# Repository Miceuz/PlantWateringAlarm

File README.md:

PlantWateringAlarm
==================

A soil moisture level sensor based on ATTINY44. Uses capacitive sensing.

More info at http://wemakethings.net/chirp

Contact: mic a wemakethings.net

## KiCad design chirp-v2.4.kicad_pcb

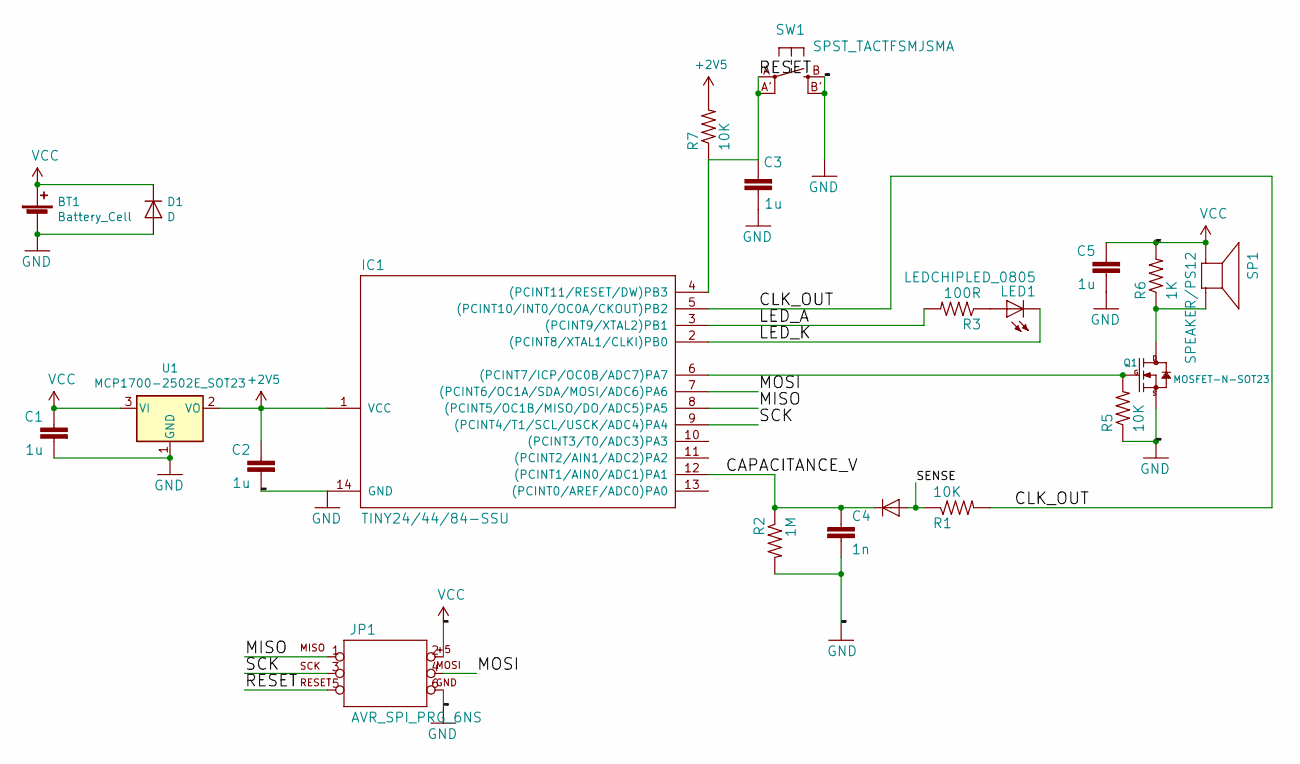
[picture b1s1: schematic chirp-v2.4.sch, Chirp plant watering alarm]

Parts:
BT1: Battery_Cell
C1: 1u; C_0603_1608Metric; PartNo ?
C2, C3, C5: 1u; C_0603_1608Metric
C4: 1n; C_0603_1608Metric
D1: D
D2: DIODE-SCHOTTKY_; SOD-523; PartNo ?
IC1: TINY24/44/84-SSU; SOIC-14_3.9x8.7mm_Pitch1.27mm; PartNo ?
JP1: AVR_SPI_PRG_6NS; 2X3-NS
LED1: LEDCHIPLED_0805; CHIPLED_0805
Q1: MOSFET-N-SOT23; SOT-23
R1, R5, R7: 10K; R_0603_1608Metric
R2: 1M; R_0603_1608Metric; PartNo ?
R3: 100R; R_0603_1608Metric
R6: 1K; R_0603_1608Metric
SP1: SPEAKER/PS12; PS12
SW1: SPST_TACTFSMJSMA; FSMJSMA
U1: MCP1700-2502E_SOT23; SOT-23; PartNo ?

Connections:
+2V5: C2.1, IC1.1 (VCC), R7.2, U1.2 (VO)
/CAPACITANCE_V: C4.1, D2.K (C), IC1.12 ((PCINT1/AIN0/ADC1)PA1), R2.1
/CLK_OUT: IC1.5 ((PCINT10/INT0/OC0A/CKOUT)PB2), R1.2
/LED_A: IC1.3 ((PCINT9/XTAL2)PB1), R3.2
/LED_K: IC1.2 ((PCINT8/XTAL1/CLKI)PB0), LED1.C
/MISO: IC1.8 ((PCINT5/OC1B/MISO/DO/ADC5)PA5), JP1.1
/MOSI: IC1.7 ((PCINT6/OC1A/SDA/MOSI/ADC6)PA6), JP1.4
/RESET: C3.1, IC1.4 ((PCINT11/RESET/DW)PB3), JP1.5, R7.1, SW1.A, SW1.A' (P1)
/SCK: IC1.9 ((PCINT4/T1/SCL/USCK/ADC4)PA4), JP1.3
/SENSE: D2.A, R1.1
GND: BT1.2 (-), C1.2, C2.2, C3.2, C4.2, C5.2, D1.2 (A), IC1.14 (GND), JP1.6, Q1.2 (S), R2.2, R5.1, SW1.B (S), SW1.B' (S1), U1.1 (GND)
unnamed: IC1.6 ((PCINT7/ICP/OC0B/ADC7)PA7), Q1.1 (G), R5.2
unnamed: LED1.A, R3.1
unnamed: Q1.3 (D), R6.1, SP1.P$2 (-)
VCC: BT1.1 (+), BT1.3, C1.1, C5.1, D1.1 (K), JP1.2, R6.2, SP1.P$1 (+), U1.3 (VI)

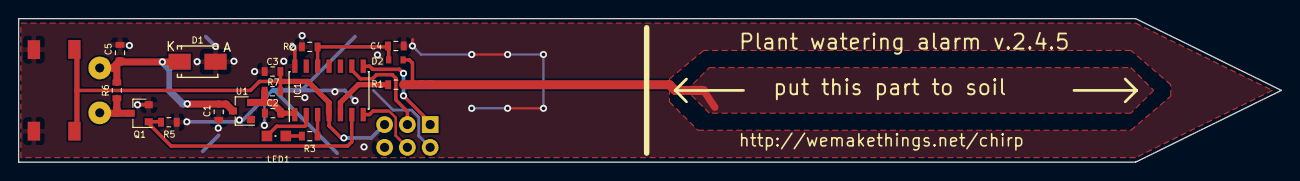
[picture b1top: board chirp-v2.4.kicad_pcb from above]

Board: 2 copper layers, 140.8 x 16.0 mm, 21 parts (0 on the bottom side), 15 nets.

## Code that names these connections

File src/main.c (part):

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#include <avr/eeprom.h>
#include "usiTwiSlave.h"

#define USI_SCK PA4
#define USI_MISO PA5
#define USI_CS PA6
#define BUZZER PA7
#define BUTTON PB2
#define LED_K PB0 
#define LED_A PB1

//------------ peripherals ----------------

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}

void inline ledOff() {
  DDRB &= ~(_BV(LED_A) | _BV(LED_K)); //make pins inputs
  PORTB &= ~(_BV(LED_A) | _BV(LED_K));//disable pullups
}

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    DDRA |= _BV(BUZZER);   //piezo buzzer
    PORTA &= ~_BV(BUZZER);
    
    DDRB |= _BV(PB0);   //nothing
    PORTB &= ~_BV(PB0);
    DDRB |= _BV(PB1);   //nothing
    PORTB &= ~_BV(PB1);
    DDRB |= _BV(PB2);   //square wave output
    PORTB &= ~_BV(PB2);
}

void inline setupPowerSaving() {
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    uint16_t result = getADC1();
    
    stopExcitationSignal();
    PORTB &= ~_BV(PB2);
    PRR |= _BV(PRTIM0);
    
    ADCSRA &=~ _BV(ADEN);
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    TCCR1A = 0;
    TCCR1B = _BV(CS12);					//start timer1 with prescaler clk/256
    
    PCMSK1 |= _BV(PCINT8); 				//enable pin change interrupt on LED_K
    GIMSK |= _BV(PCIE1); 
    lightCycleOver = 0;
    while(!lightCycleOver) {
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
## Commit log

2012-08-02 initial board and schematics
2012-08-02 git ignore
2012-09-07 +firmware, thicker traces, etc
2012-09-16 +power saving
2012-09-29 mainly current test setup code, some power saving directives commented out
2012-09-29 working on v2.1 and v2.2 - low pass filter based setup. various sensor designs for testing
2012-09-29 enable clock output on PB2
2012-09-30 defines for pins according to function
2012-10-03 all the v2.2 changes + light sensor
2012-10-23 v2.3 ordered from seeed
2012-10-23 Licensed under CERN OHL v.1.1
2012-11-28 final touches before production
2012-11-28 start working on finalization of firmware
2012-11-30 state machine implemented - 4 levels of operation depending how dry soil is
2012-11-30 ignore *i *s
2012-12-05 fiddling with the thresholds
2012-12-05 minor spelling fixes
2012-12-05 moved the insertion line a bit further, moved components away from the soil, made a new order at seeed
2012-12-05 more readme
2013-06-09 less frightened margins
2013-06-10 change SPI to I2C
2013-06-10 USI driver
2013-06-10 add schematics pic for eagle free people
2013-07-14 add twi driver to makefile
2013-07-14 fix thresholds, tune up sensor mode
2013-10-27 a new board design
2014-01-08 rollback previous commit to main.c as it was just testing mode code
2014-01-17 schematics png updated
2014-02-17 Don't switch OSC speed as it cretes problems in sensor mode. Run everything at 2Mhz. Chirp sound has changed, but oh well. Turn the thresholds all the way down. For plants that are watered more often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
2014-02-17 shuffle code around to look nicer
2014-02-17 put direcotry in to some order
2014-02-19 leave led connected to ground while discharging
2014-02-19 schematics in b/w
2014-04-28 quick and dirty sensor mode. works as expected
2014-05-04 code cleanup, fix so it realy works, light measurement is done asynchroneously
2014-05-13 fix a bug which prevented using I2C adresses with MSB set, probably it was because Arduino sets up SDA too soon and there is a shady STOP condition detection in START interrupt handler. Added more st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
2014-05-13 Don't blink leds as this interferes with light measurement
2014-05-17 v-scoring instead of routing
2014-08-05 Add bitrate setting to makefile
2014-09-03 Add sensor schematics and PCB drawings
2014-11-23 erase eeprom while flashing, allow eeprom erasing in fuses
2014-11-23 on the first startup expect full darkness and calibrate to that, save light threshold to eeprom
2014-11-24 let the light threshold be 10% from total darkness
2014-11-25 add programmer jig firmware
2014-11-25 add some pics
2014-11-29 finally I2C comm works. damn third party libraries
2014-11-29 add I2C command to return the firmware version
2014-11-29 add testing functionality, update firmware to sensor v2.1
2014-12-02 less wait before programming, put the right firmware image into the programmer
2015-03-10 Don't allow the address to be set 0
2015-07-02 Measure light less, smaller delay
2015-12-13 Be more verbose when avrduding
2015-12-13 Move Chirp layout to KiCad. Finally.
2016-02-23 Add manufacturing set, tune up the silkscreen on the board
2016-05-11 Some test data
2017-08-30 Fix inline function declarations, preserve eeprom upon flashing
2018-02-19 Add some means to detect battery level, not working yet
2018-03-13 Play around with excitation signal settings, make excitation signal start from the very begining, avoid long delays in capacitance measurement. Non working unfortunately
2018-03-13 Shorten the measurement time as we change the capacitor to a smaller one. Avoid ADC sleep as it stops the excitation timer
2018-03-22 Erase eeprom on reflash. Blink led before chirping
2018-03-23 Fix a bug with adc mux selection. Add debug output. Make it work? Maybe?
2018-03-23 Invert the capasitanceDiff logic, play with sleep time constants and thresholds, change the playHappy logic
2018-03-23 measure ref voltage during the whork also
2018-03-23 refactor battery measurement
2018-03-23 Refactor adcOn and Off, some small refactorings
2018-03-23 Refactor calibration routines and do full sleep outside of the if structure
2018-03-23 fix adc turn off by setuping power saving just before the main loop, set ref capacitance closest to measurement events so that it's more similar to initial measurements
2018-03-23 Firmatting fixes
2018-03-23 Make some functions inline, extract a playHappy method
2018-03-23 Even more inlining of functions
2018-03-23 Refactor the logic as a state machine in a switch statement. Expermental
2018-03-27 Refactor entering to hibernate
2018-03-27 Add soft uart library for debug purposes
2018-03-27 Allow newer C syntax, add debug output
2018-03-27 Add hardware changes - add U1 LDO regulator, connect ISP VCC to battery, update cap values, update footprints, update routing, update battery footprint
2019-02-23 Prohibit setting i2c addresses > 127
    i2c addresses are 7 bits, where the 8th bit is reserved by the protocol to indicate whether reading or writing is intended.
2020-04-08 Fix a grave bug where hibernate counter was 8bit when total counts were 16bit. Add debug printing for monitoring
2021-09-30 add missing include
2023-06-06 typos, twink
